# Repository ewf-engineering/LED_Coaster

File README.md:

# LED_Coaster
 
kicad tutorial:
https://www.youtube.com/watch?v=aVUqaB0IMh4

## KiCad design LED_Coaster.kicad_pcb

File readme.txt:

kicad tutorial:
https://www.youtube.com/watch?v=aVUqaB0IMh4

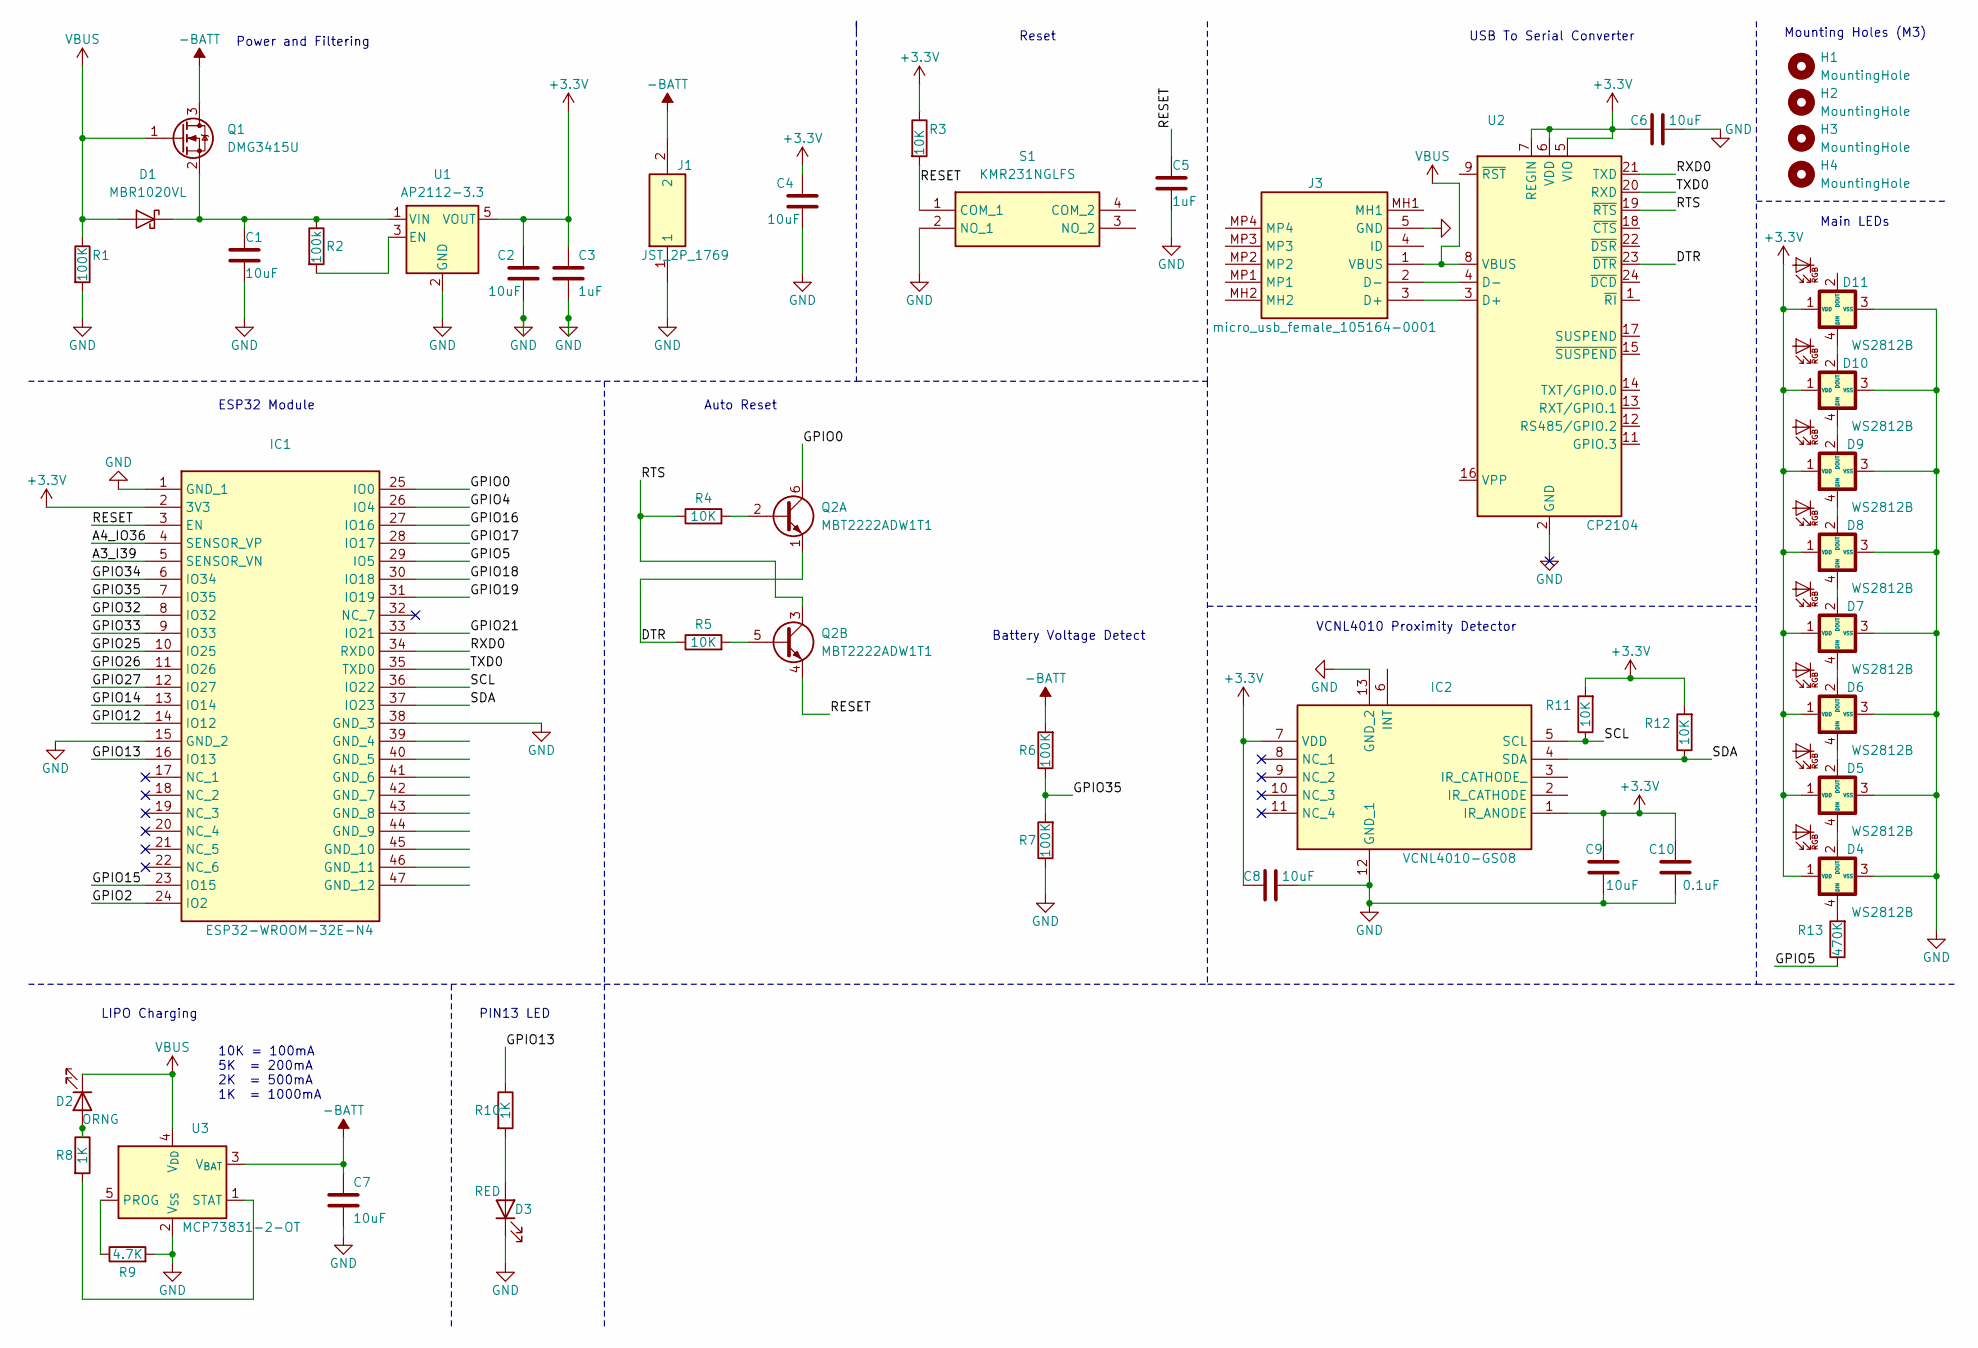
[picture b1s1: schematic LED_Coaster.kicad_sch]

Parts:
C1, C2, C4, C6, C8, C9: 10uF; C_0603_1608Metric
C3: 1uF; C_0402_1005Metric
C5: 1uF; C_0603_1608Metric
C7: 10uF; C_0402_1005Metric
C10: 0.1uF; C_0603_1608Metric
D1: MBR1020VL; D_SOD-123F
D2: ORNG; D_0805_2012Metric
D3: RED; D_0805_2012Metric
D4, D5, D6, D7, D8, D9, D10, D11: WS2812B; LED_WS2812B_PLCC4_5.0x5.0mm_P3.2mm
H1, H2, H3, H4: MountingHole; MountingHole_3.2mm_M3
IC1: ESP32-WROOM-32E-N4; ESP32WROOM32EN4; Mouser Part Number 356-ESP32WRM32E132PH
IC2: VCNL4010-GS08; VCNL4010GS08; Mouser Part Number 78-VCNL4010-GS08
J1: JST_2P_1769; 1769; Mouser Part Number 485-1769
J3: micro_usb_female_105164-0001; 1051640001; Mouser Part Number 538-105164-0001
Q1: DMG3415U; SOT-23
Q2: MBT2222ADW1T1; SOT-363_SC-70-6
R1, R6, R7: 100K; R_0402_1005Metric
R2: 100k; R_0402_1005Metric
R3, R4, R5, R11, R12: 10K; R_0402_1005Metric
R8, R10: 1K; R_0402_1005Metric
R9: 4.7K; R_0402_1005Metric
R13: 470K; R_0402_1005Metric
S1: KMR231NGLFS; Mouser Part Number 611-KMR231NGLFS
U1: AP2112-3.3; SOT-23-5
U2: CP2104; QFN-24-1EP_4x4mm_P0.5mm_EP2.6x2.6mm
U3: MCP73831-2-OT; SOT-23-5

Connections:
+3.3V: C2.1, C3.1, C4.1, C6.1, C8.1, C9.2, C10.2, D4.1 (VDD), D5.1 (VDD), D6.1 (VDD), D7.1 (VDD), D8.1 (VDD), D9.1 (VDD), D10.1 (VDD), D11.1 (VDD), IC1.2 (3V3), IC2.1 (IR_ANODE), IC2.7 (VDD), R3.1, R11.2, R12.2, U1.5 (VOUT), U2.5 (VIO), U2.6 (VDD), U2.7 (REGIN)
/A3_I39: IC1.5 (SENSOR_VN)
/A4_IO36: IC1.4 (SENSOR_VP)
/DTR: Q2.1 (E1), R5.1, U2.23 (~DTR)
/GPIO0: IC1.25 (IO0), Q2.6 (C1)
/GPIO2: IC1.24 (IO2)
/GPIO4: IC1.26 (IO4)
/GPIO5: IC1.29 (IO5), R13.1
/GPIO12: IC1.14 (IO12)
/GPIO13: IC1.16 (IO13), R10.1
/GPIO14: IC1.13 (IO14)
/GPIO15: IC1.23 (IO15)
/GPIO16: IC1.27 (IO16)
/GPIO17: IC1.28 (IO17)
/GPIO18: IC1.30 (IO18)
/GPIO19: IC1.31 (IO19)
/GPIO21: IC1.33 (IO21)
/GPIO25: IC1.10 (IO25)
/GPIO26: IC1.11 (IO26)
/GPIO27: IC1.12 (IO27)
/GPIO32: IC1.8 (IO32)
/GPIO33: IC1.9 (IO33)
/GPIO34: IC1.6 (IO34)
/GPIO35: IC1.7 (IO35), R6.1, R7.2
/RESET: C5.1, IC1.3 (EN), Q2.4 (E2), R3.2, S1.1 (COM_1)
/RTS: Q2.3 (C2), R4.1, U2.19 (~RTS)
/RXD0: IC1.34 (RXD0), U2.21 (TXD)
/SCL: IC1.36 (IO22), IC2.5 (SCL), R11.1
/SDA: IC1.37 (IO23), IC2.4 (SDA), R12.1
/TXD0: IC1.35 (TXD0), U2.20 (RXD)
/VBATT: C7.1, J1.2, Q1.3 (D), R6.2, U3.3 (V_{BAT})
GND: C1.2, C2.2, C3.2, C4.2, C5.2, C6.2, C7.2, C8.2, C9.1, C10.1, D3.1 (K), D4.3 (VSS), D5.3 (VSS), D6.3 (VSS), D7.3 (VSS), D8.3 (VSS), D9.3 (VSS), D10.3 (VSS), D11.3 (VSS), IC1.1 (GND_1), IC1.15 (GND_2), IC1.38 (GND_3), IC2.12 (GND_1), IC2.13 (GND_2), J1.1, J3.5 (GND), R1.2, R7.1, R9.2, S1.2 (NO_1), U1.2 (GND), U2.2 (GND), U2.25 (GND), U3.2 (V_{SS})
unnamed: C1.1, D1.1 (K), Q1.2 (S), R2.1, U1.1 (VIN)
unnamed: D2.2 (A), R8.1
unnamed: D3.2 (A), R10.2
unnamed: D4.4 (DIN), R13.2
unnamed: D4.2 (DOUT), D5.4 (DIN)
unnamed: D5.2 (DOUT), D6.4 (DIN)
unnamed: D6.2 (DOUT), D7.4 (DIN)
unnamed: D7.2 (DOUT), D8.4 (DIN)
unnamed: D8.2 (DOUT), D9.4 (DIN)
unnamed: D9.2 (DOUT), D10.4 (DIN)
unnamed: D10.2 (DOUT), D11.4 (DIN)
unnamed: J3.3 (D+), U2.3 (D+)
unnamed: J3.2 (D-), U2.4 (D-)
unnamed: Q2.2 (B1), R4.2
unnamed: Q2.5 (B2), R5.2
unnamed: R2.2, U1.3 (EN)
unnamed: R9.1, U3.5 (PROG)
unnamed: R8.2, U3.1 (STAT)
VBUS: D1.2 (A), D2.1 (K), J3.1 (VBUS), Q1.1 (G), R1.1, U2.8 (VBUS), U3.4 (V_{DD})

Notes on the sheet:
Reset
VCNL4010 Proximity Detector
LIPO Charging
USB To Serial Converter
PIN13 LED
10K = 100mA 5K = 200mA 2K = 500mA 1K = 1000mA
ESP32 Module
Auto Reset
Main LEDs
Mounting Holes (M3)
Power and Filtering
Battery Voltage Detect

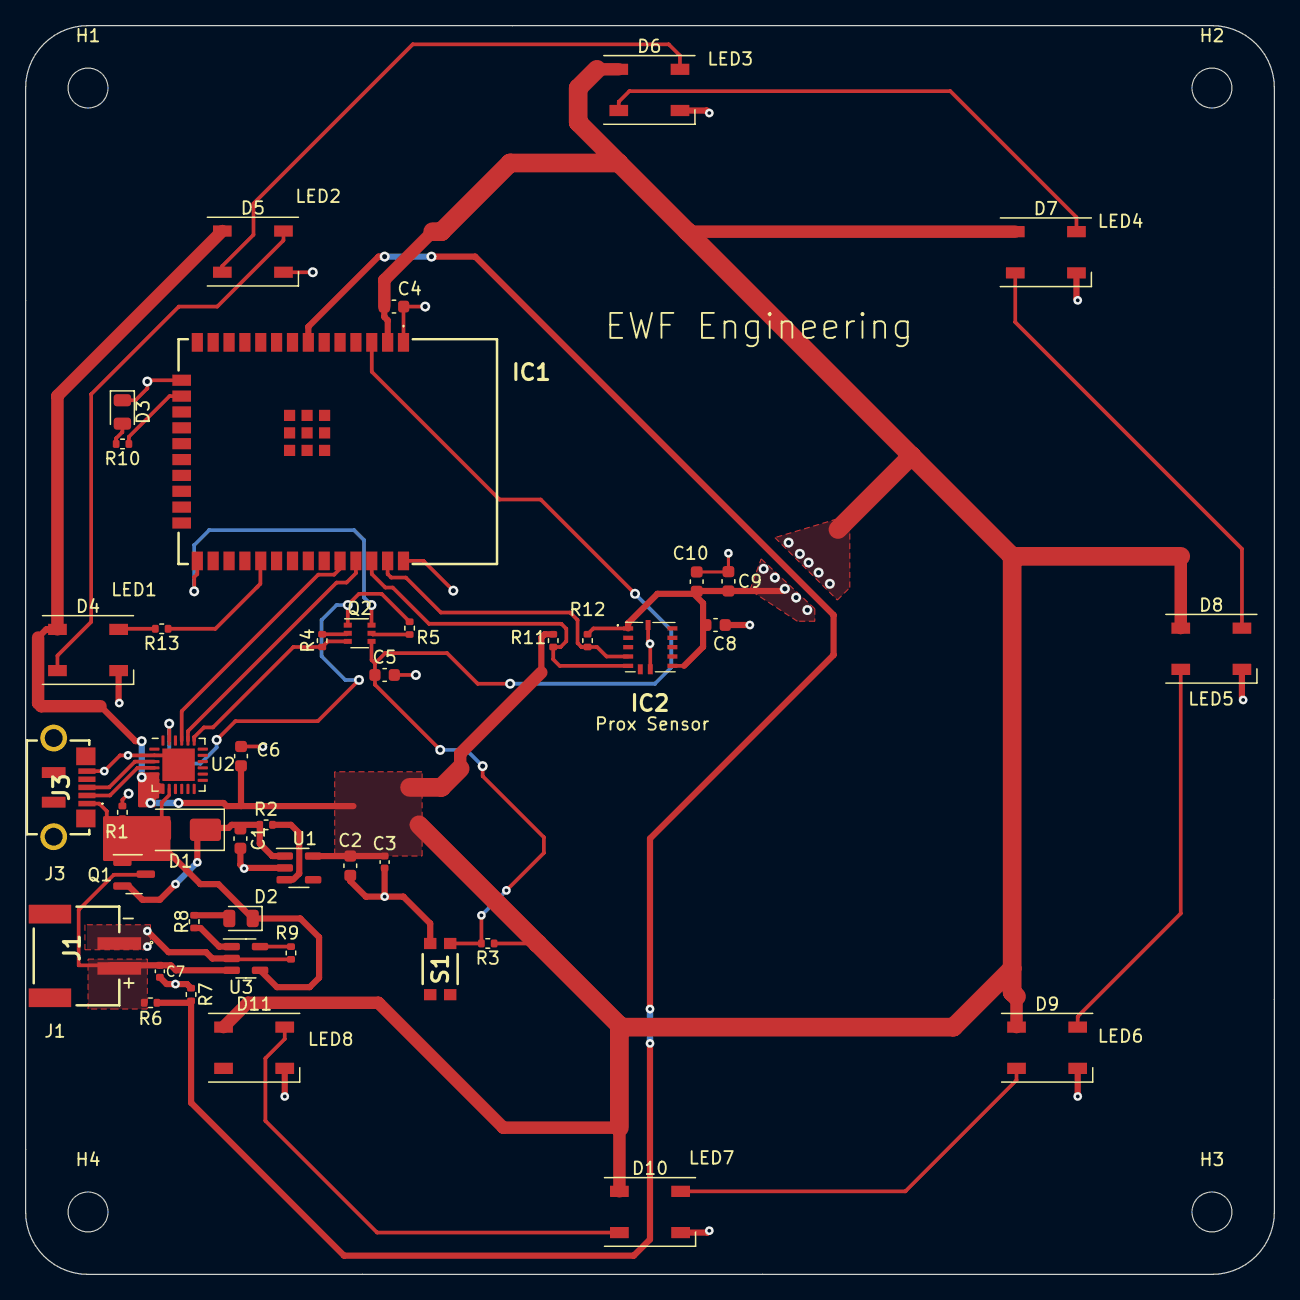
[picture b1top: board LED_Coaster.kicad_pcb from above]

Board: 2 copper layers, 100.0 x 100.0 mm, 48 parts (0 on the bottom side), 33 nets.

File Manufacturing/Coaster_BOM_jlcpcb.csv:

Comment,Designator,Footprint
10uF,"C1, C2, C4, C6, C8, C9",Capacitor_SMD:C_0603_1608Metric
1uF,C3,Capacitor_SMD:C_0402_1005Metric
1uF,C5,Capacitor_SMD:C_0603_1608Metric
10uF,C7,Capacitor_SMD:C_0402_1005Metric
0.1uF,C10,Capacitor_SMD:C_0603_1608Metric
MBR1020VL,D1,Diode_SMD:D_SOD-123F
ORNG,D2,Diode_SMD:D_0805_2012Metric
RED,D3,Diode_SMD:D_0805_2012Metric
WS2812B,"D4, D5, D6, D7, D8, D9, D10, D11",LED_SMD:LED_WS2812B_PLCC4_5.0x5.0mm_P3.2mm
MountingHole,"H1, H2, H3, H4",MountingHole:MountingHole_3.2mm_M3
ESP32-WROOM-32E-N4,IC1,ESP32_WROOM_32E_N4:ESP32WROOM32EN4
VCNL4010-GS08,IC2,VCNL4010-GS08:VCNL4010GS08
JST_2P_1769,J1,JST_2Pin_1769:1769
micro_usb_female_105164-0001,J3,1051640001
DMG3415U,Q1,Package_TO_SOT_SMD:SOT-23
MBT2222ADW1T1,Q2,Package_TO_SOT_SMD:SOT-363_SC-70-6
100K,"R1, R6, R7",Resistor_SMD:R_0402_1005Metric
100k,R2,Resistor_SMD:R_0402_1005Metric
10K,"R3, R4, R5, R11, R12",Resistor_SMD:R_0402_1005Metric
1K,"R8, R10",Resistor_SMD:R_0402_1005Metric
4.7K,R9,Resistor_SMD:R_0402_1005Metric
470K,R13,Resistor_SMD:R_0402_1005Metric
KMR231NGLFS,S1,KMR231NGLFS:KMR231NGLFS
AP2112-3.3,U1,Package_TO_SOT_SMD:SOT-23-5
CP2104,U2,Package_DFN_QFN:QFN-24-1EP_4x4mm_P0.5mm_EP2.6x2.6mm
MCP73831-2-OT,U3,Package_TO_SOT_SMD:SOT-23-5

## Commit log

2023-12-29 Initial Commit
    Rev 0.1
2024-01-05 Rerouted some traces, changed diode to a standard 0.7/0.8V drop, tried to improve power routing. Fixed "-VBATT" to "+VBATT"
    My work is a bit messy still, but it should be fine like this. Still haven't done the math on the LDO, need to figure out what the power of the system is.
2024-01-06 Incorrect sch file was uploaded
